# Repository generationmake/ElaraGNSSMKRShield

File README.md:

# ElaraGNSSMKRShield
GNSS Shield with Wuerth Elara for Arduino MKR

## pin usage

### Arduino MKR connector CN1

| **Pin** | **Pin Name** | **Signal**    | **Description**                        |
|:-------:|:------------:|:-------------:|:--------------------------------------:|
| 1       | AREF         |               |                                        |
| 2       | DAC0/A0      |               |                                        |
| 3       | A1           |               |                                        |
| 4       | A2           |               |                                        |
| 5       | A3           |               |                                        |
| 6       | A4           |               |                                        |
| 7       | A5           |               |                                        |
| 8       | A6           |               |                                        |
| 9       | 0            | WAKE_UP       | wake signal to Elara GNSS              |
| 10      | 1            | 1PPS          | 1PPS signal from Elara GNSS            |
| 11      | 2            |               |                                        |
| 12      | 3            |               |                                        |
| 13      | 4            |               |                                        |
| 14      | 5            | ON_OFF        | switch Elara GNSS on and off           |
| 15      | 6            |               |                                        |
| 16      | 7            |               |                                        |
| 17      | 8/MOSI       |               |                                        |
| 18      | 9/SCK        |               |                                        |
| 19      | 10/MISO      |               |                                        |
| 20      | 11/SDA       | I2C_SDA       | to Elara GNSS if I2C option is used    |
| 21      | 12/SCL       | I2C_SCL       | to Elara GNSS if I2C option is used    |
| 22      | 13/RX        | SERIAL_RX     | to Elara GNSS if serial option is used |
| 23      | 14/TX        | SERIAL_TX     | to Elara GNSS if serial option is used |
| 24      | RESET        |               |                                        |
| 25      | GND          | GND           |                                        |
| 26      | VCC          | 3V3-rail      | supply voltage for board               |
| 27      | VIN          |               |                                        |
| 28      | 5V0          |               |                                        |

### SMA connector CN2

SMA coax connector.

| **Pin** | **Signal**    | **Description**                  |
|:-------:|:-------------:|:--------------------------------:|
| center  | 1PPS          |                                  |
| shield  | GND           |                                  |

## PCB

### Top

### Bottom

## Variants

By default the Elara GNSS is connected via I2C. It is possible to connect to serial.

### BOM changes

The following parts need to be changed:

| part | I2C variant | serial variant |
|:----:|:-----------:|:--------------:|
| R2   | 10k         | DNI            |
| R3   | DNI         | 10k            |
| R9   | 0R          | DNI            |
| R10  | 0R          | DNI            |
| R11  | DNI         | 0R             |
| R12  | DNI         | 0R             |

## Resources

### Datasheets

 * https://www.we-online.de/katalog/de/ELARA-I
 
 ### Arduino Libraries

* [107-Arduino-NMEA-Parser](https://github.com/107-systems/107-Arduino-NMEA-Parser)

## License

This hardware is licensed under the CERN OHL v. 1.2

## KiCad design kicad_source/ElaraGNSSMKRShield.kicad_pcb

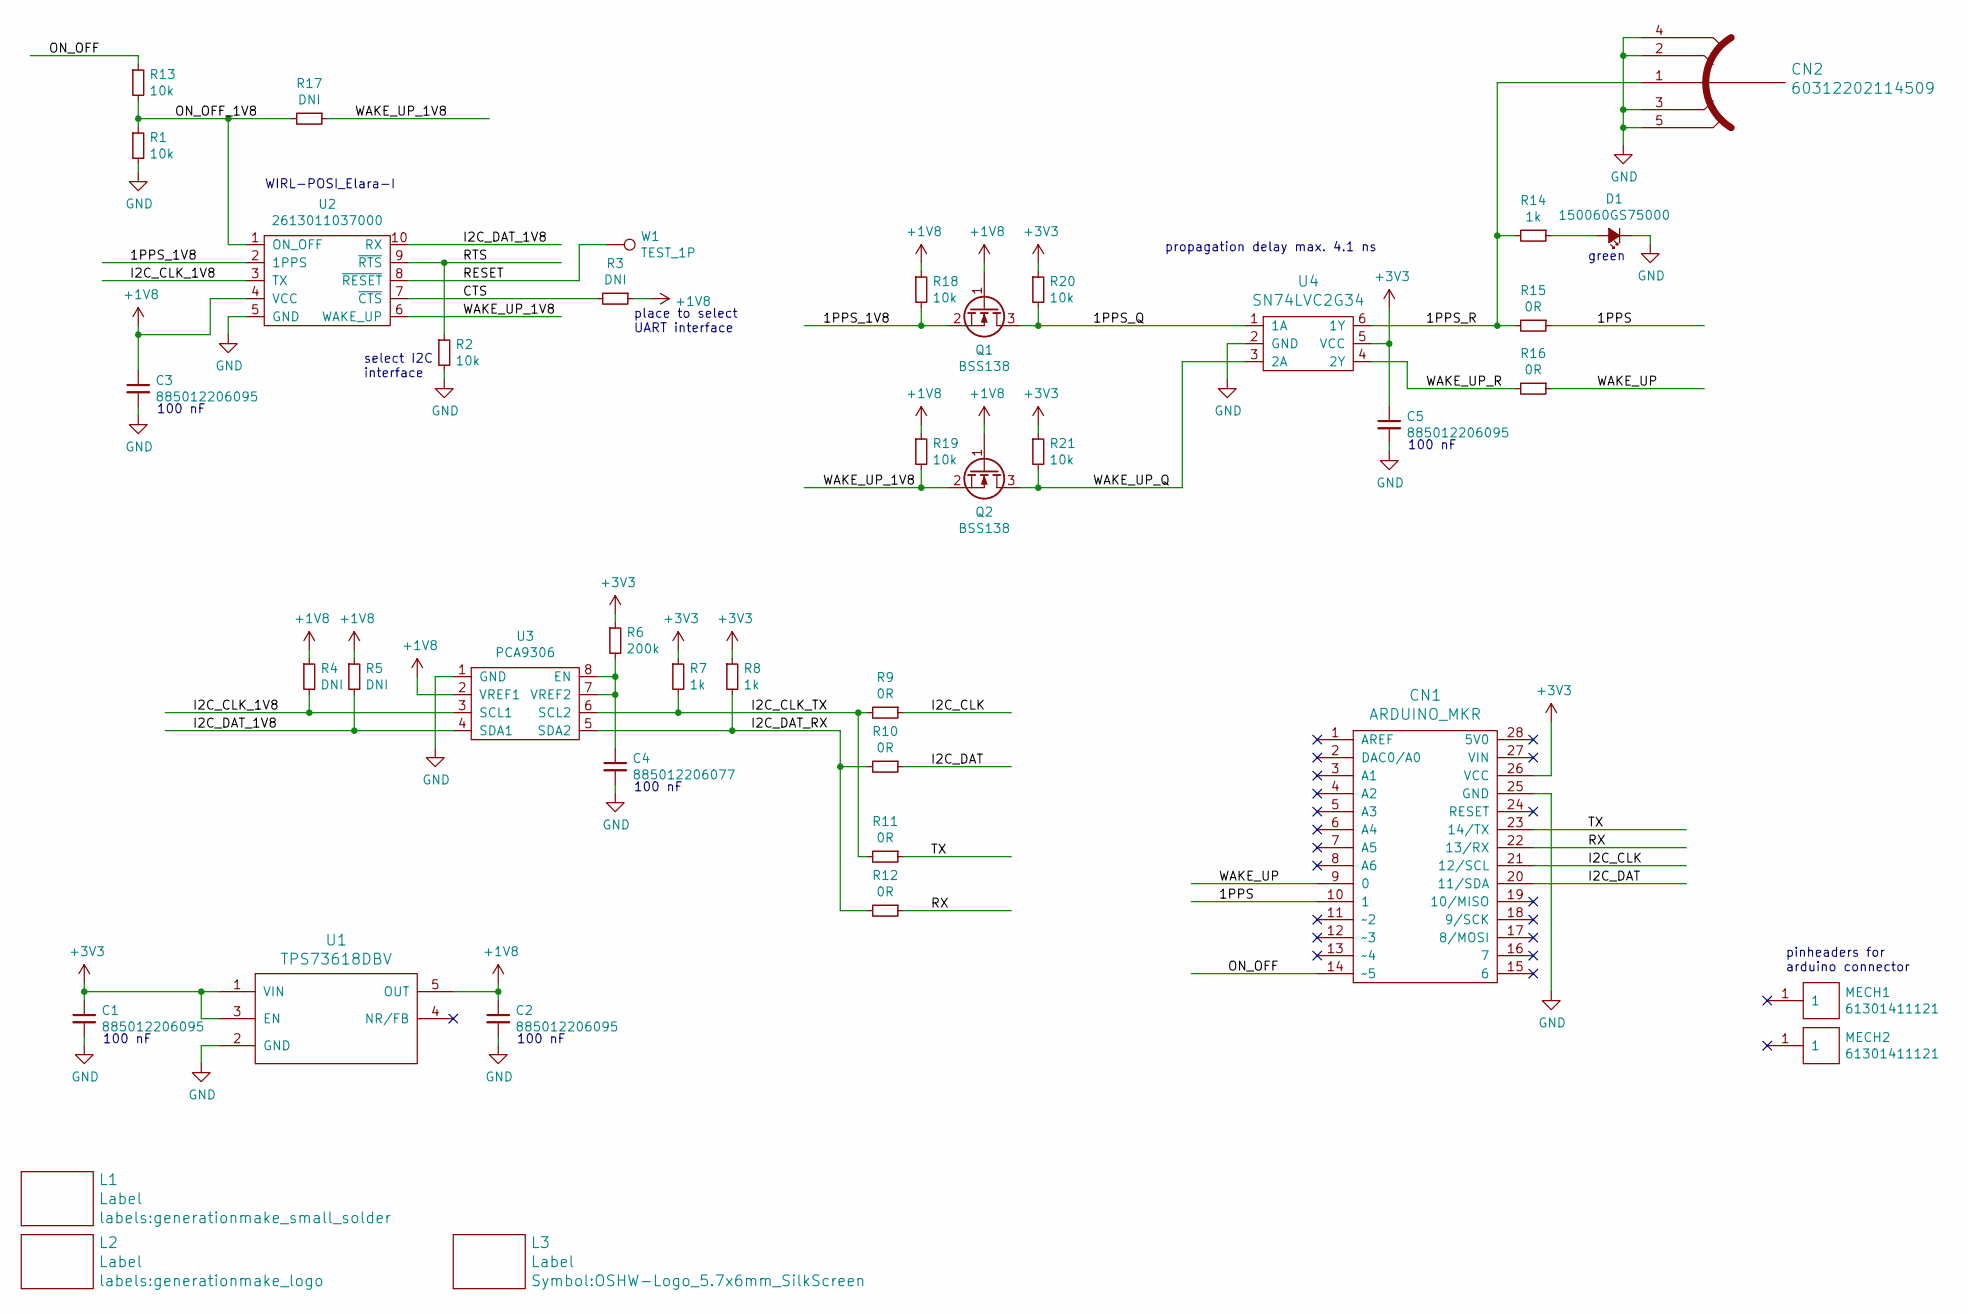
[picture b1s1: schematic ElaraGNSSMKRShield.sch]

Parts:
C1, C2, C3, C5: 885012206095; C_0603
C4: 885012206077; C_0603
CN1: ARDUINO_MKR; ARDUINO_MKR_HOLES_PINHEADER_EDGE
CN2: 60312202114509; WR-SMA-PCB
D1: 150060GS75000; LED_0603
L1: Label; generationmake_small_solder
L2: Label; generationmake_logo
L3: Label; OSHW-Logo_5.7x6mm_SilkScreen
MECH1, MECH2: 61301411121
Q1, Q2: BSS138; SOT-23
R1, R2, R13, R18, R19, R20, R21: 10k; R_0603
R3, R4, R5, R17: DNI; R_0603
R6: 200k; R_0603
R7, R8, R14: 1k; R_0603
R9, R10, R11, R12, R15, R16: 0R; R_0603
U1: TPS73618DBV; SOT-23-5
U2: 2613011037000; wuerth_WIRL-POSI_Elara-I
U3: PCA9306; TSSOP-8_3x3mm_Pitch0.65mm
U4: SN74LVC2G34; SOT-23-6
W1: TEST_1P; SolderWirePad_single_1mmSMD

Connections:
+1V8: C2.1, C3.1, Q1.1 (G), Q2.1 (G), R3.1, R4.1, R5.1, R18.1, R19.1, U1.5 (OUT), U2.4 (VCC), U3.2 (VREF1)
+3V3: C1.1, C5.1, CN1.26 (VCC), R6.1, R7.1, R8.1, R20.1, R21.1, U1.1 (VIN), U1.3 (EN), U4.5 (VCC)
/1PPS: CN1.10 (1), R15.1
/1PPS_1V8: Q1.2 (S), R18.2, U2.2 (1PPS)
/1PPS_Q: Q1.3 (D), R20.2, U4.1 (1A)
/1PPS_R: CN2.1, R14.2, R15.2, U4.6 (1Y)
/CTS: R3.2, U2.7 (~CTS)
/I2C_CLK: CN1.21 (12/SCL), R9.1
/I2C_CLK_1V8: R4.2, U2.3 (TX), U3.3 (SCL1)
/I2C_CLK_TX: R7.2, R9.2, R11.2, U3.6 (SCL2)
/I2C_DAT: CN1.20 (11/SDA), R10.1
/I2C_DAT_1V8: R5.2, U2.10 (RX), U3.4 (SDA1)
/I2C_DAT_RX: R8.2, R10.2, R12.2, U3.5 (SDA2)
/ON_OFF: CN1.14 (~~5), R13.1
/ON_OFF_1V8: R1.1, R13.2, R17.2, U2.1 (ON_OFF)
/RESET: U2.8 (~RESET), W1.1
/RTS: R2.1, U2.9 (~RTS)
/RX: CN1.22 (13/RX), R12.1
/TX: CN1.23 (14/TX), R11.1
/WAKE_UP: CN1.9 (0), R16.1
/WAKE_UP_1V8: Q2.2 (S), R17.1, R19.2, U2.6 (WAKE_UP)
/WAKE_UP_Q: Q2.3 (D), R21.2, U4.3 (2A)
/WAKE_UP_R: R16.2, U4.4 (2Y)
GND: C1.2, C2.2, C3.2, C4.2, C5.2, CN1.25 (GND), CN2.2, CN2.3, CN2.4, CN2.5, D1.1 (K), R1.2, R2.2, U1.2 (GND), U2.5 (GND), U3.1 (GND), U4.2 (GND)
unnamed: C4.1, R6.2, U3.7 (VREF2), U3.8 (EN)
unnamed: D1.2 (A), R14.1

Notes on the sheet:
select I2C interface
place to select UART interface
propagation delay max. 4.1 ns
green
100 nF
WIRL-POSI_Elara-I
pinheaders for arduino connector

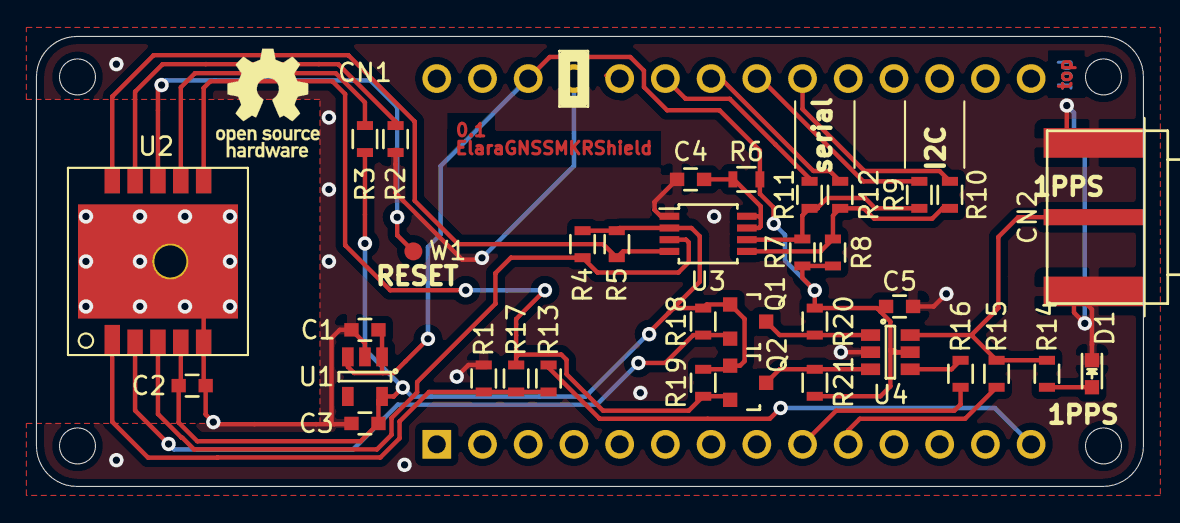
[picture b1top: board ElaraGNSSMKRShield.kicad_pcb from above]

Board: 2 copper layers, 61.5 x 25.0 mm, 39 parts (1 on the bottom side), 26 nets.

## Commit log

2020-11-15 added kicad project
2020-11-15 updated schematic and board
2020-11-15 generated schematic pdf and image
2020-11-15 updated level shifter circuit
2020-11-16 beautified layout, added images, updated files
2020-12-21 added wuerth part numbers
2020-12-22 updated shape of PCB
2020-12-22 added licence information
2020-12-22 updated schematic pdf

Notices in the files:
kicad_source/ElaraGNSSMKRShield.kicad_pcb:
Licensed under CERN OHL v.1.2
